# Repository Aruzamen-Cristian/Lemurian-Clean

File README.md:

# Lemurian Clean

### Descripción del Proyecto

Lemurian Clean es una solución autónoma y eficiente para la recogida de desechos en cuerpos de agua. Equipado con una cámara ESP-CAM y hélices para su movilidad, el robot navega por el agua recogiendo desechos con una cinta transportadora.

### Características Principales

**Cámara ESP-CAM:** Proporciona capacidad de visión para la navegación y detección de desechos.

**Propulsión con Hélices:** Permite un movimiento eficiente y controlado en el agua.

**Cinta Transportadora:** Recolecta desechos desde la superficie del agua y los almacena en un contenedor interno.

### Hardware del Proyecto

-  **ESP32-CAM:** Proporciona capacidad de visión para la navegación y detección de desechos.

-  **ESP32:** Utiliza un ESP32 para controlar los drivers y motores del robot, asegurando una operación eficiente y precisa.

-  **Motores y Hélices:** Para la propulsión del robot.

- **Cinta Transportadora:** Para la recogida de basura.

- **Chasis y Carcasa:** Estructura resistente al agua y flotante.

### Código del Robot
Podes encontrar el código completo del robot en la carpeta `Codigo LC` del repositorio.

#### Función de Callback para Bluetooth

```c
void callback_function(esp_spp_cb_event_t event, esp_spp_cb_param_t *param) {
  if (event == ESP_SPP_START_EVT) {
    Serial.println("Inicializado SPP");
  } else if (event == ESP_SPP_SRV_OPEN_EVT) {
    Serial.println("Cliente conectado");
  } else if (event == ESP_SPP_CLOSE_EVT) {
    Serial.println("Cliente desconectado");
  } else if (event == ESP_SPP_DATA_IND_EVT) {
    Serial.println("Datos recibidos"); 
    while (BT.available()) {     // Mientras haya datos por recibir
      int incoming = BT.read();  // Lee un byte de los datos recibidos
    }
  }
}
```
> Explicacion:
Esta función maneja diferentes eventos del Bluetooth, como la inicialización, conexión y recepción de datos. Es crucial para interactuar con dispositivos Bluetooth.

#### Función setup()
```c
void setup() {
  Serial.begin(115200);     // Inicializando la conexión serial para debug
  BT.begin("ESP32_HOA");  // Nombre de tu Dispositivo Bluetooth y en modo esclavo
  Serial.println("El dispositivo Bluetooth está listo para emparejar");
  BT.register_callback(callback_function);  // Registramos la función "callback_function" como función callback.

  pinMode(Motor1a, OUTPUT);
  pinMode(Motor1b, OUTPUT);
  pinMode(Motor2a, OUTPUT);
  pinMode(Motor2b, OUTPUT);
	scale.begin(LOADCELL_DOUT_PIN, LOADCELL_SCK_PIN); 
	scale.set_scale(-471.497);
	scale.tare();
```
> Explicación:
> Inicialización Serial y Bluetooth: Se inicializa la comunicación serial para debug y la comunicación Bluetooth con el nombre "ESP32_HOA".
> Configuración de Pines: Se configuran los pines de los motores como salidas.
> Inicialización del Sensor: Se inicializa el sensor de celda de carga y se calibra la escala.

#### Función loop()
```c
void loop() {
  if (BT.available())  // Compruebe si recibimos algo de Bluetooth
  {
    int incoming = BT.read();  // Lee lo que recibimos
    Serial.print("Recibido: ");
    Serial.println(incoming);
    switch (incoming) {
      case 70:  // F en ASCII
        Adelante();
        break;
      case 66:  // B en ASCII
        Retroceder();
        break;
      case 76:     // L en ASCII
        Izquierda();
        break;
      case 82:  // R en ASCII
        Derecha();
        break;
      case 40:
        Serial.print("Primer Lectura:\t");
        Serial.print(scale.get_units(), 1);
        scale.power_down();
        scale.power_up();
        break;
      case 48:  // Velocidad 0
        veloc = 0;
        break;
      case 49:  // Velocidad 1
        veloc = 25;
        break;
      // Otros casos para velocidades
      default:
        Parar();
        break;
    }
  }
}

```
> Explicación:
Recepción de Comandos: La función `loop()` verifica si se han recibido datos por Bluetooth y actúa según el comando recibido. Dependiendo del comando, se ejecutan funciones para mover el robot hacia adelante, atrás, izquierda, derecha, o detenerse.

#### Funciones de Control de Motores
```c
void Adelante() {
  digitalWrite(Motor1a, HIGH);
  digitalWrite(Motor1b, LOW);
  digitalWrite(Motor2a, HIGH);
  digitalWrite(Motor2b, LOW);
}
void Retroceder() {
  digitalWrite(Motor1a, LOW);
  digitalWrite(Motor1b, HIGH);
  digitalWrite(Motor2a, LOW);
  digitalWrite(Motor2b, HIGH);
}
void Izquierda() {
  digitalWrite(Motor1a, LOW);
  digitalWrite(Motor1b, HIGH);
  digitalWrite(Motor2a, HIGH);
  digitalWrite(Motor2b, LOW);
}
void Derecha() {
  digitalWrite(Motor1a, HIGH);
  digitalWrite(Motor1b, LOW);
  digitalWrite(Motor2a, LOW);
  digitalWrite(Motor2b, HIGH);
}
void Parar() {
  digitalWrite(Motor1a, LOW);
  digitalWrite(Motor1b, LOW);
  digitalWrite(Motor2a, LOW);
  digitalWrite(Motor2b, LOW);
}

```

> Explicación:
Control de Motores: Estas funciones controlan la dirección de los motores para mover el robot hacia adelante, atrás, izquierda, derecha, o detenerlo. Usan `digitalWrite()`para cambiar el estado de los pines.

### Diseño del PCB
Los archivos del diseño del PCB están ubicados en la carpeta `PCB`. Puedes descargar los archivos y el diagrama esquemático para fabricar y ensamblar tu propia placa.

> PCBv4 Capa Superior

> PCBv4 Capa Inferior

### Uso
1. Encender el robot y asegurarse de que todos los sistemas están operativos.

3. Colocar el robot en el agua y activarlo.

5. Supervisar su operación a través de la cámara ESP-CAM y ajustar si es necesario.

#### Contacto
Para más información o preguntas sobre Lemurian Clean, puedes contactarnos en [ aruzamencristianmarcelo@gmail.com ], [damian34casas@gmail.com].

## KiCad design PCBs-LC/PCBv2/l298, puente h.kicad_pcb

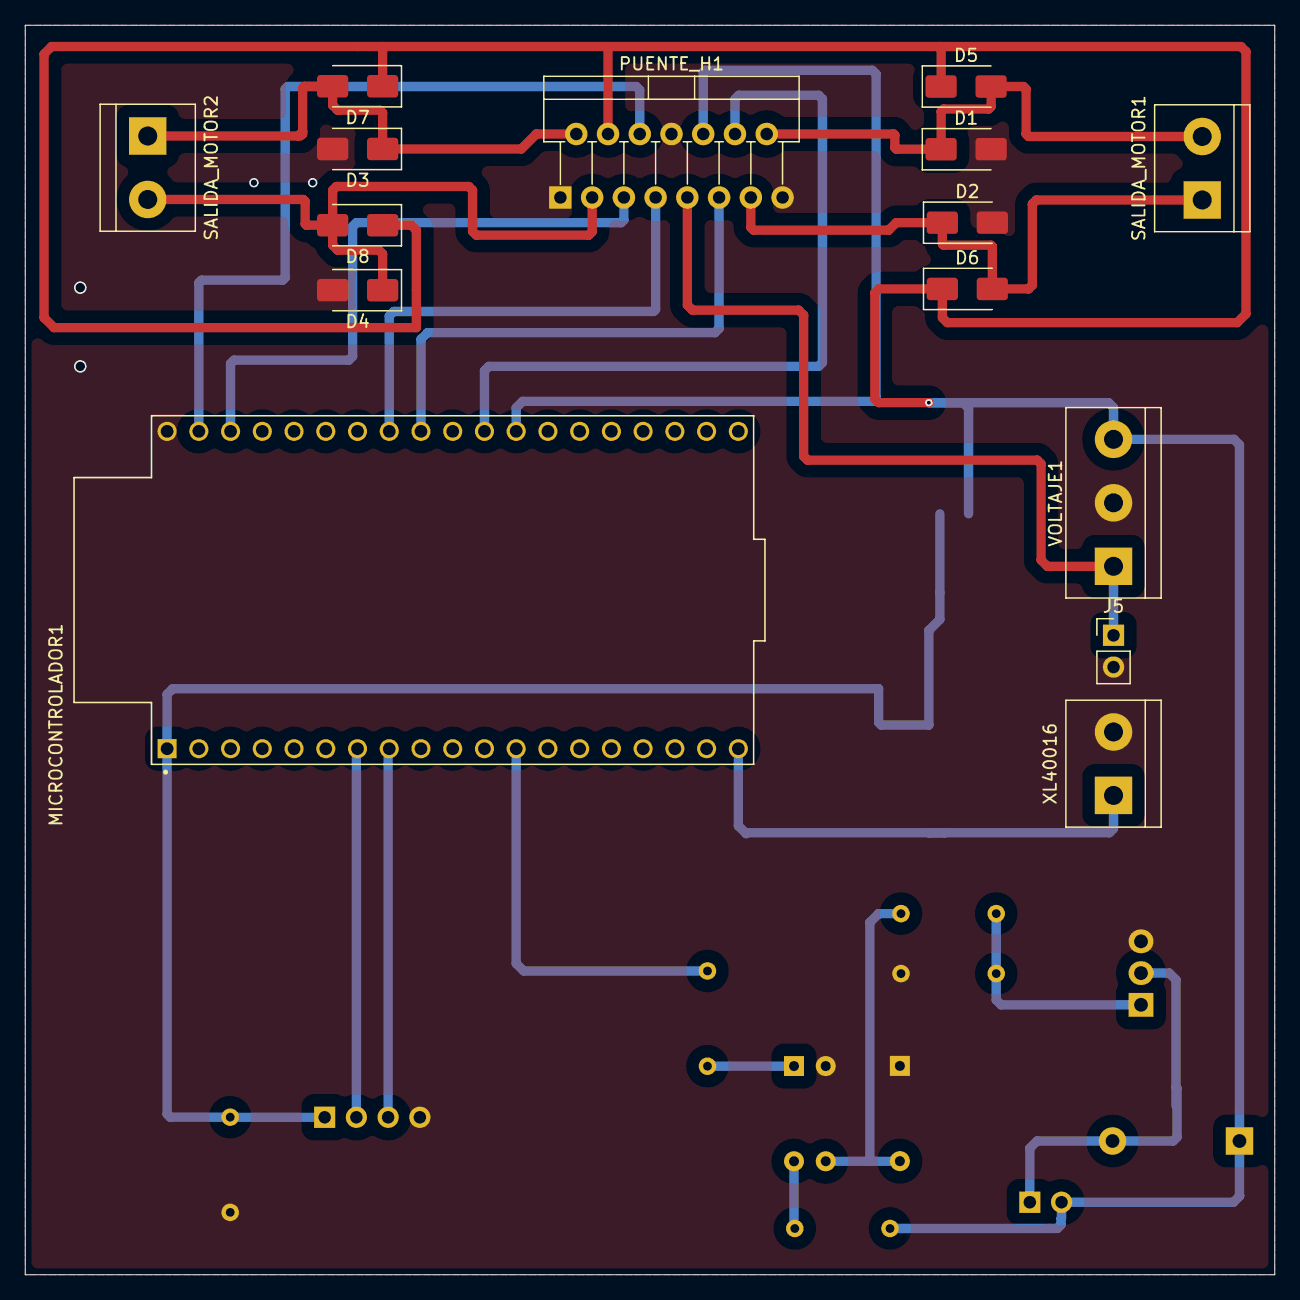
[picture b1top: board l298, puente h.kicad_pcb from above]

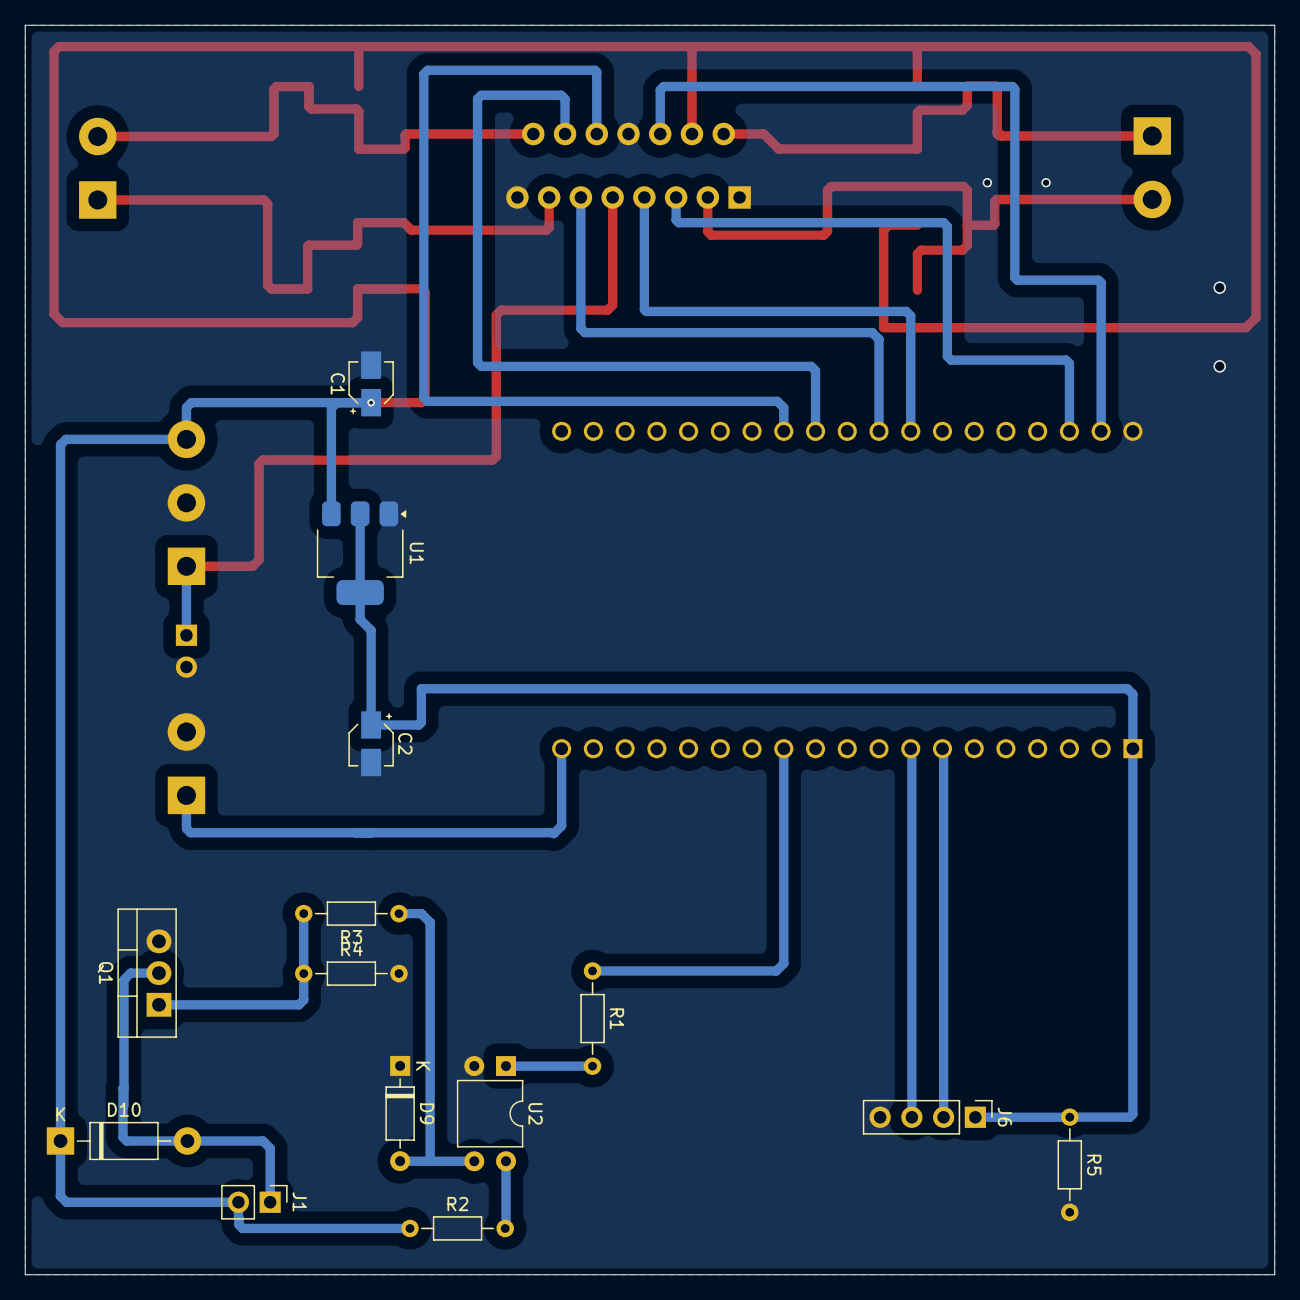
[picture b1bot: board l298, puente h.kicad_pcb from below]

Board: 2 copper layers, 100.0 x 100.0 mm, 29 parts (14 on the bottom side), 23 nets.

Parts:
C1, C2: 220; CP_Elec_3x5.3
D1, D2, D3, D4, D5, D6, D7, D8: 1N4148WT; D_SMA
D9: 1N4148; D_DO-35_SOD27_P7.62mm_Horizontal
D10: 1N4007; D_DO-41_SOD81_P10.16mm_Horizontal
J1: MOTOR_CINTA; PinHeader_1x02_P2.54mm_Vertical
J5: PinHeader_1x02_P2.54mm_Vertical
J6: PinHeader_1x04_P2.54mm_Vertical
MICROCONTROLADOR1: ESP32_DEVKITC; MODULE_ESP32-DEVKITC
PUENTE_H1: L298N; TO-220-15_P2.54x2.54mm_StaggerOdd_Lead4.58mm_Vertical
Q1: IRF540N; TO-220-3_Vertical
R1: 1K; R_Axial_DIN0204_L3.6mm_D1.6mm_P7.62mm_Horizontal
R2, R4: 4,7K; R_Axial_DIN0204_L3.6mm_D1.6mm_P7.62mm_Horizontal
R3: 100; R_Axial_DIN0204_L3.6mm_D1.6mm_P7.62mm_Horizontal
R5: 1k; R_Axial_DIN0204_L3.6mm_D1.6mm_P7.62mm_Horizontal
SALIDA_MOTOR1, SALIDA_MOTOR2: TerminalBlock_bornier-2_P5.08mm
U1: AMS1117; SOT-223-3_TabPin2
U2: PC817; DIP-4_W7.62mm
VOLTAJE1: TerminalBlock_bornier-3_P5.08mm
XL40016: TerminalBlock_bornier-2_P5.08mm

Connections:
3,3V: C2.1, J6.1, MICROCONTROLADOR1.1 (3V3), R5.1, U1.2 (VO)
+5V: J5.1, PUENTE_H1.9 (Vss), VOLTAJE1.1
+12V: C1.1, D5.1 (K), D6.1 (K), D7.1 (K), D8.1 (K), D10.1 (K), J1.2, PUENTE_H1.4 (Vs), R2.1, U1.3 (VI), VOLTAJE1.3
DT: J6.2, MICROCONTROLADOR1.7 (IO32)
EnA: MICROCONTROLADOR1.37 (IO23), PUENTE_H1.6 (EnA)
EnB: MICROCONTROLADOR1.30 (IO18), PUENTE_H1.11 (EnB)
GND: C1.2, C2.2, D1.2 (A), D2.2 (A), D3.2 (A), D4.2 (A), D9.1 (K), J5.2, J6.4, MICROCONTROLADOR1.38 (GND), PUENTE_H1.1 (SENSE_A), PUENTE_H1.8 (GND), PUENTE_H1.15 (SENSE_B), Q1.3 (S), R4.2, R5.2, U1.1 (ADJ), U2.2, VOLTAJE1.2, XL40016.2
IN1: MICROCONTROLADOR1.36 (IO22), PUENTE_H1.5 (IN1)
IN2: MICROCONTROLADOR1.31 (IO19), PUENTE_H1.7 (IN2)
IN3: MICROCONTROLADOR1.27 (IO16), PUENTE_H1.10 (IN3)
IN4: MICROCONTROLADOR1.28 (IO17), PUENTE_H1.12 (IN4)
unnamed: D9.2 (A), R3.1, U2.3
unnamed: D10.2 (A), J1.1, Q1.2 (D)
unnamed: Q1.1 (G), R3.2, R4.1
unnamed: R1.2, U2.1
unnamed: R2.2, U2.4
OUT1: D3.1 (K), D7.2 (A), PUENTE_H1.2 (OUT1), SALIDA_MOTOR2.1
OUT2: D4.1 (K), D8.2 (A), PUENTE_H1.3 (OUT2), SALIDA_MOTOR2.2
OUT3: D2.1 (K), D6.2 (A), PUENTE_H1.13 (OUT3), SALIDA_MOTOR1.1
OUT4: D1.1 (K), D5.2 (A), PUENTE_H1.14 (OUT4), SALIDA_MOTOR1.2
PWM: MICROCONTROLADOR1.12 (IO14), R1.1
SCK: J6.3, MICROCONTROLADOR1.8 (IO33)
Vin: MICROCONTROLADOR1.19 (5V), XL40016.1

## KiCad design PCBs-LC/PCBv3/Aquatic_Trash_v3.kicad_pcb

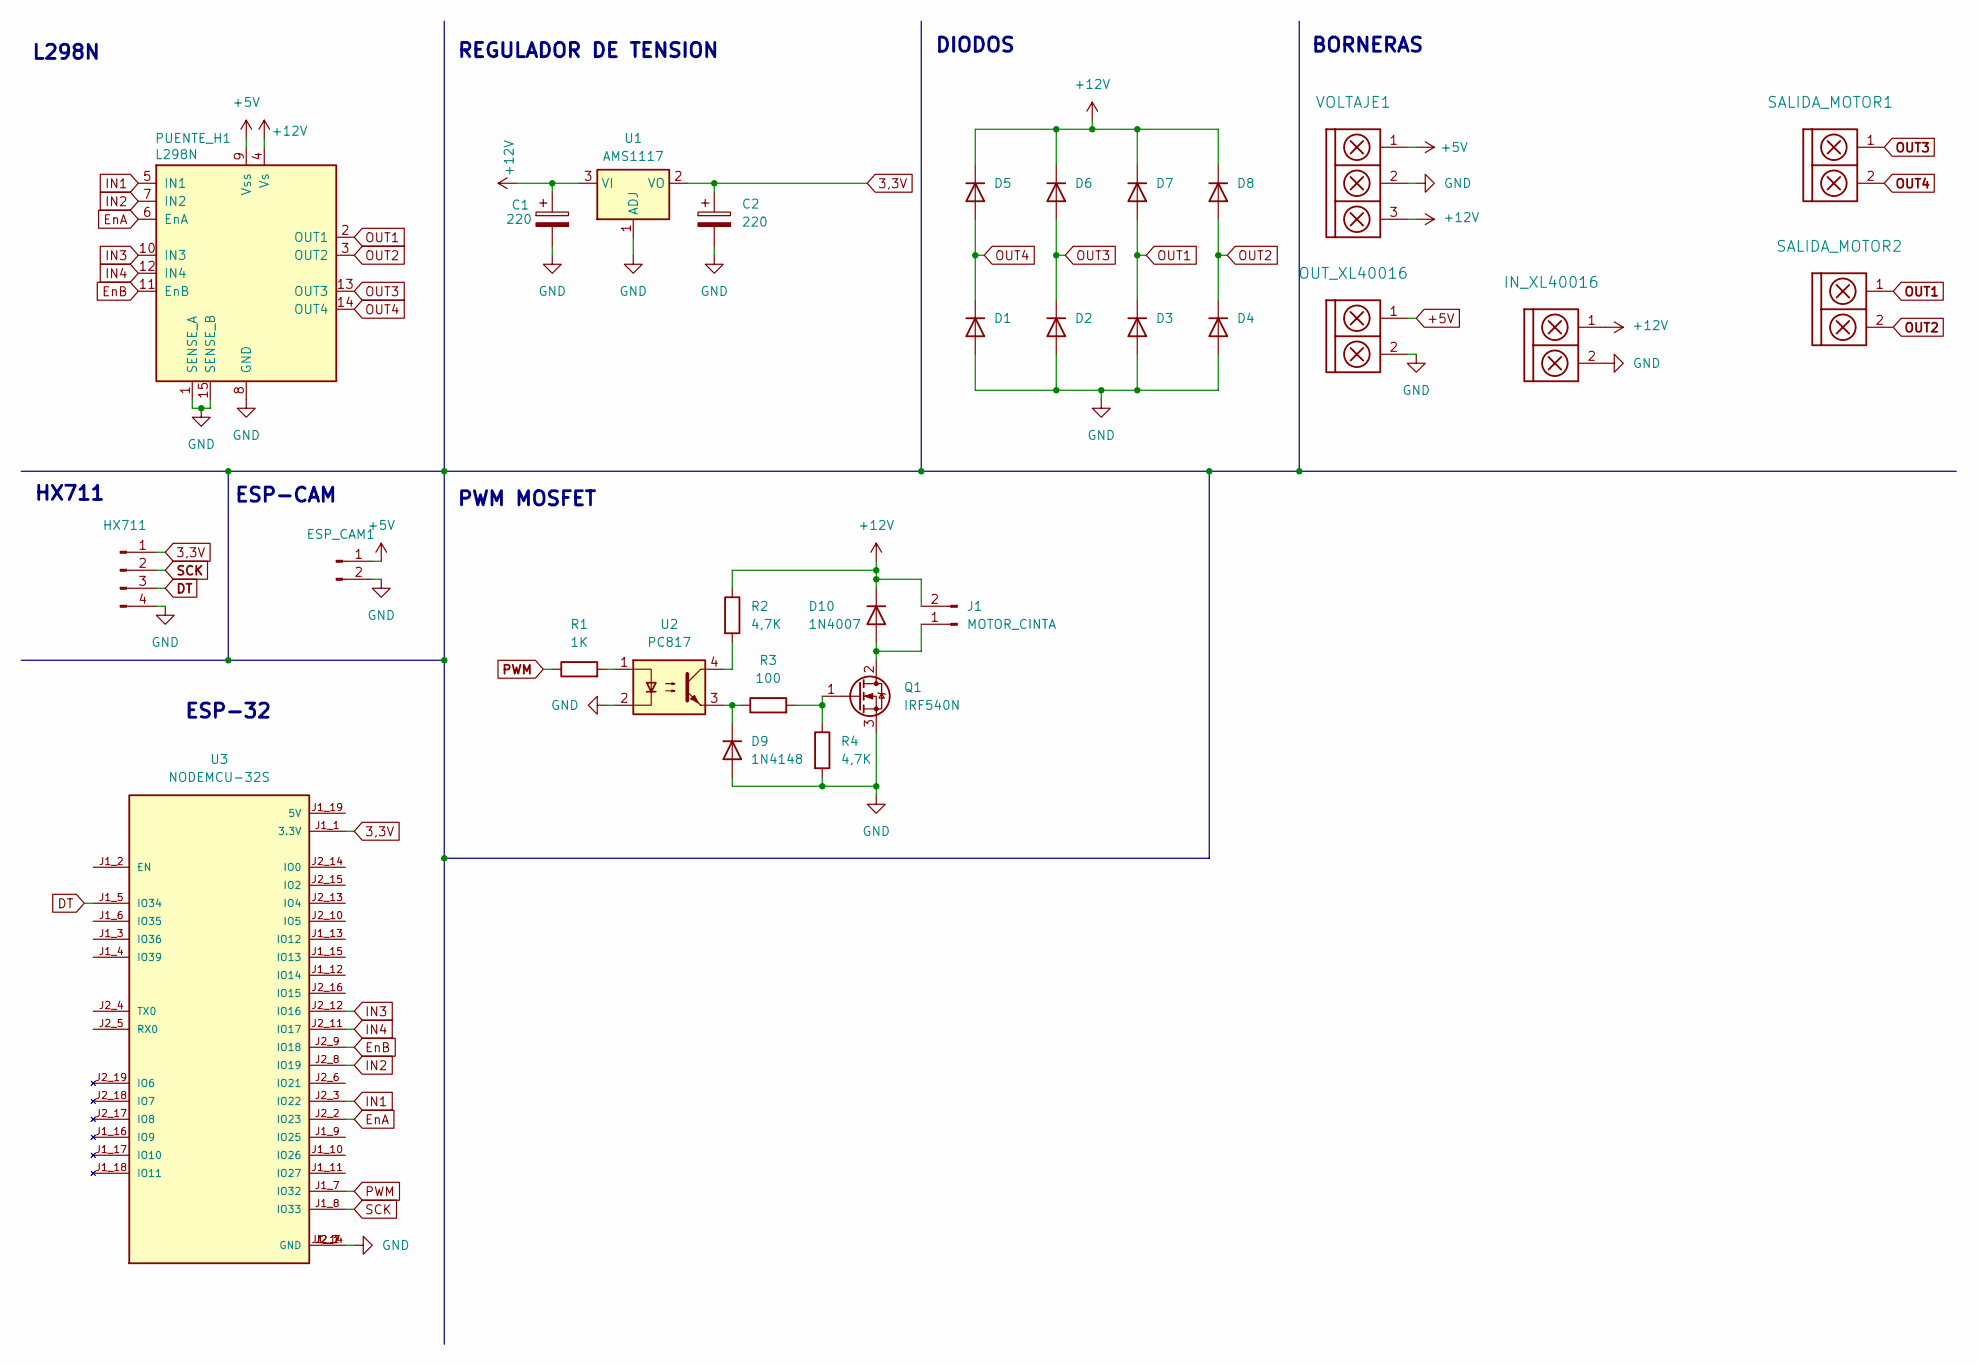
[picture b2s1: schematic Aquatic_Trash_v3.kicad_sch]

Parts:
C1, C2: 220; CP_Elec_8x10.5
D1, D2, D3, D4, D5, D6, D7, D8: 1N4148WT; D_SMA
D9: 1N4148; D_SMA
D10: 1N4007; D_SMA
ESP_CAM1: PinHeader_1x02_P2.54mm_Vertical
HX711: PinHeader_1x04_P2.54mm_Vertical
IN_XL40016: TerminalBlock_bornier-2_P5.08mm
J1: MOTOR_CINTA; PinHeader_1x02_P2.54mm_Vertical
OUT_XL40016: TerminalBlock_bornier-2_P5.08mm
PUENTE_H1: L298N; TO-220-15_P2.54x2.54mm_StaggerOdd_Lead4.58mm_Vertical
Q1: IRF540N; TO-220-3_Vertical
R1: 1K; R_0805_2012Metric
R2, R4: 4,7K; R_0805_2012Metric
R3: 100; R_0805_2012Metric
SALIDA_MOTOR1, SALIDA_MOTOR2: TerminalBlock_bornier-2_P5.08mm
U1: AMS1117; SOT-223-3_TabPin2
U2: PC817; DIP-4_W7.62mm
U3: NODEMCU-32S; MODULE_NODEMCU-32S; PARTREV V1
VOLTAJE1: TerminalBlock_bornier-3_P5.08mm

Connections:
3,3V: C2.1, HX711.1, U1.2 (VO), U3.J1_1 (3.3V)
+5V: ESP_CAM1.1, OUT_XL40016.1, PUENTE_H1.9 (Vss), U3.J1_19 (5V), VOLTAJE1.1
+12V: C1.1, D5.1 (K), D6.1 (K), D7.1 (K), D8.1 (K), D10.1 (K), IN_XL40016.1, J1.2, PUENTE_H1.4 (Vs), R2.1, U1.3 (VI), VOLTAJE1.3
DT: HX711.3, U3.J1_5 (IO34)
EnA: PUENTE_H1.6 (EnA), U3.J2_2 (IO23)
EnB: PUENTE_H1.11 (EnB), U3.J2_9 (IO18)
GND: C1.2, C2.2, D1.2 (A), D2.2 (A), D3.2 (A), D4.2 (A), D9.2 (A), ESP_CAM1.2, HX711.4, IN_XL40016.2, OUT_XL40016.2, PUENTE_H1.1 (SENSE_A), PUENTE_H1.8 (GND), PUENTE_H1.15 (SENSE_B), Q1.3 (S), R4.2, U1.1 (ADJ), U2.2, U3.J1_14 (GND), U3.J2_1 (GND), U3.J2_7 (GND), VOLTAJE1.2
IN1: PUENTE_H1.5 (IN1), U3.J2_3 (IO22)
IN2: PUENTE_H1.7 (IN2), U3.J2_8 (IO19)
IN3: PUENTE_H1.10 (IN3), U3.J2_12 (IO16)
IN4: PUENTE_H1.12 (IN4), U3.J2_11 (IO17)
unnamed: D9.1 (K), R3.1, U2.3
unnamed: D10.2 (A), J1.1, Q1.2 (D)
unnamed: Q1.1 (G), R3.2, R4.1
unnamed: R1.2, U2.1
unnamed: R2.2, U2.4
OUT1: D3.1 (K), D7.2 (A), PUENTE_H1.2 (OUT1), SALIDA_MOTOR2.1
OUT2: D4.1 (K), D8.2 (A), PUENTE_H1.3 (OUT2), SALIDA_MOTOR2.2
OUT3: D2.1 (K), D6.2 (A), PUENTE_H1.13 (OUT3), SALIDA_MOTOR1.1
OUT4: D1.1 (K), D5.2 (A), PUENTE_H1.14 (OUT4), SALIDA_MOTOR1.2
PWM: R1.1, U3.J1_7 (IO32)
SCK: HX711.2, U3.J1_8 (IO33)

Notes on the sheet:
HX711
REGULADOR DE TENSION
DIODOS
PWM MOSFET
BORNERAS
L298N
ESP-CAM
ESP-32

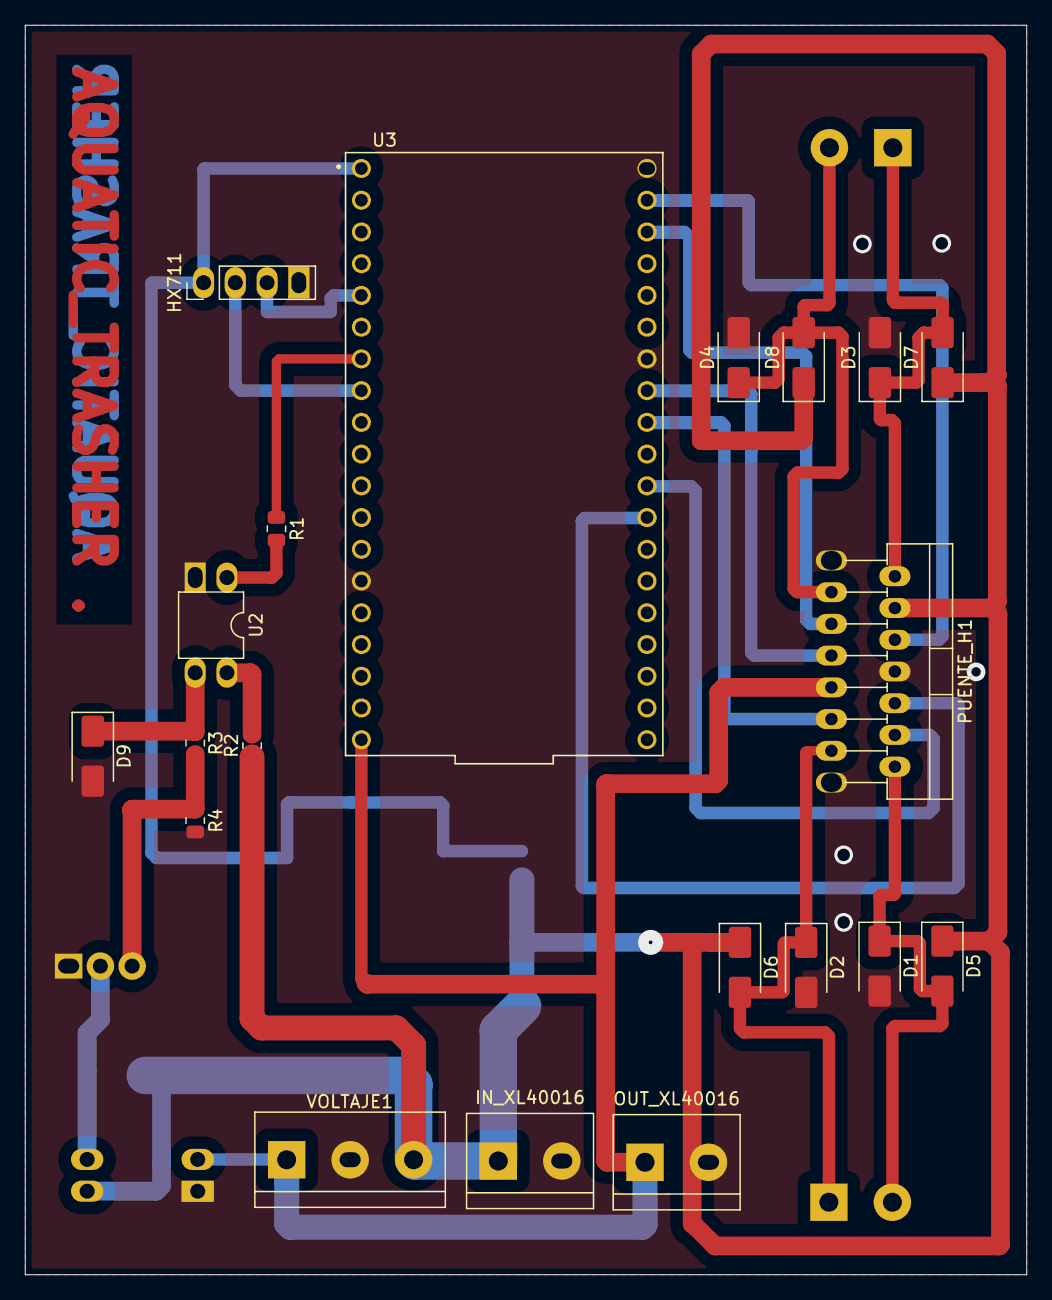
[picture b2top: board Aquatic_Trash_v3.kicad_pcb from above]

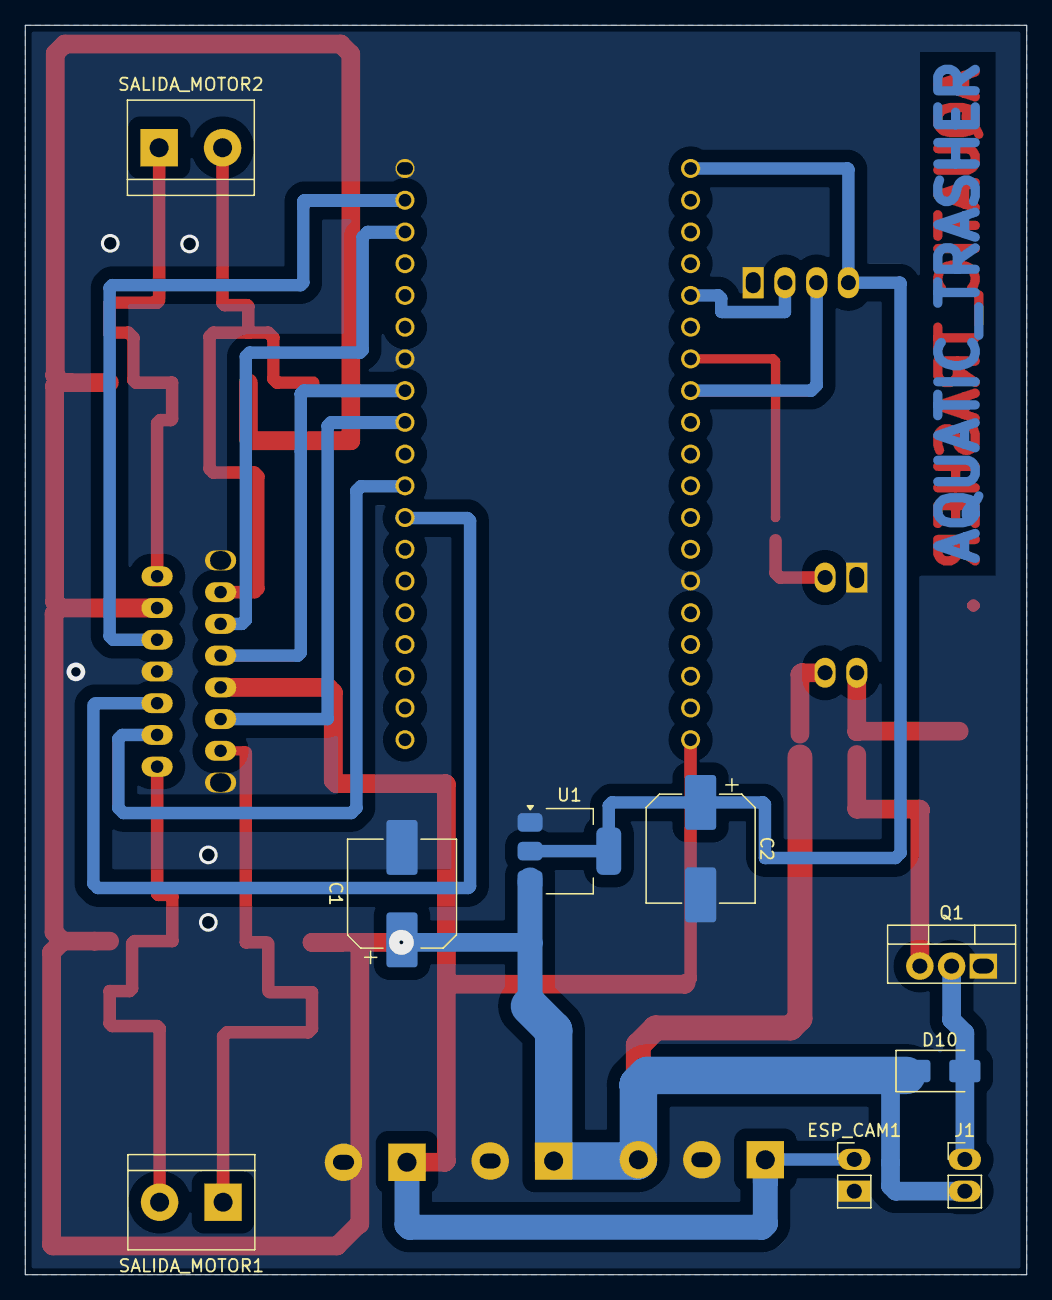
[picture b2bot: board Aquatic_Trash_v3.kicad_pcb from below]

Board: 2 copper layers, 80.2 x 100.0 mm, 29 parts (9 on the bottom side), 22 nets.

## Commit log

2024-11-29 Añade PCB
2024-11-29 Modelo3d
2024-12-02 upload PBCs
2024-12-02 Upload 3dmodels
